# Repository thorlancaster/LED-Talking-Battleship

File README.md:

# LED-Talking-Battleship
Talking Battleship implemented on a 12x12 LED grid with an ATMega328 processor

This project is composed of:
* A Control PCB that contains the main circuitry and power supplies
* A LED display PCB that drives an 12x12 grid of RGB LEDs. You'll need to make 4 of these.
* Code to run the above boards
* A compiled audio file you'll need to write to the SPI Flash chip for audio functionality
 (If you leave the flash chip blank, the game will not play audio)

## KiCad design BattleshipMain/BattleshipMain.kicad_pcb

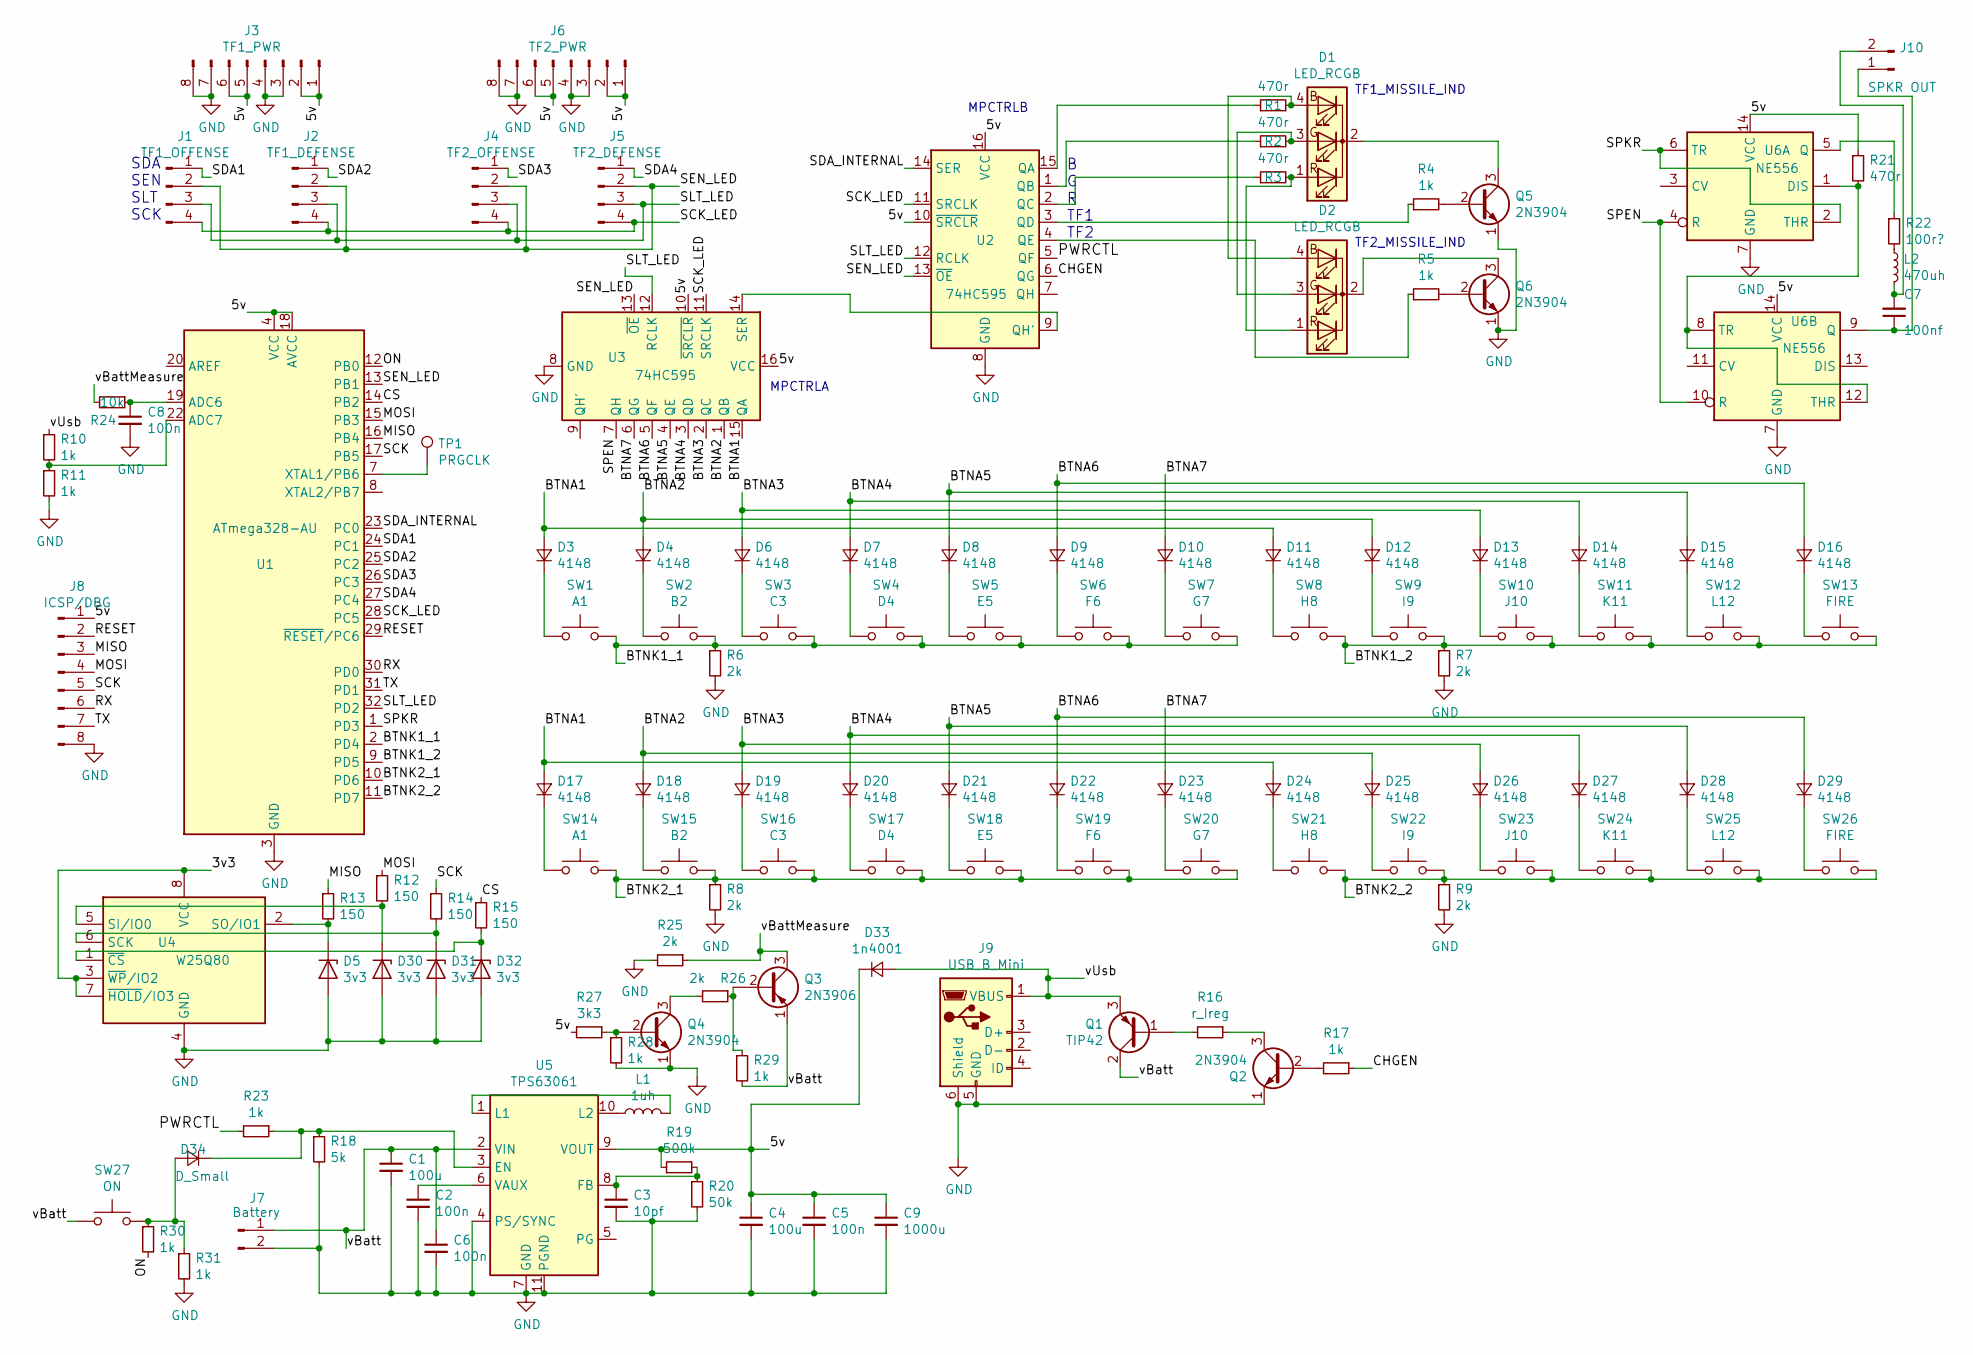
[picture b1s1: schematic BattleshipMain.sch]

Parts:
C1, C4: 100u; CP_Radial_D10.0mm_P2.50mm
C2, C5, C6, C8: 100n; C_0805_2012Metric
C3: 10pf; C_0805_2012Metric
C7: 100nf; C_0805_2012Metric
C9: 1000u; CP_Radial_D10.0mm_P7.50mm
D1, D2: LED_RCGB; LED_D5.0mm-4_RGB
D3, D4, D6, D7, D8, D9, D10, D11, D12, D13, D14, D15, D16, D17, D18, D19, D20, D21, D22, D23, D24, D25, D26, D27, D28, D29: 4148; D_DO-34_SOD68_P7.62mm_Horizontal
D5, D30, D31, D32: 3v3; D_DO-34_SOD68_P7.62mm_Horizontal
D33: 1n4001; D_DO-15_P10.16mm_Horizontal
D34: D_Small; D_DO-15_P10.16mm_Horizontal
J1: TF1_OFFENSE; PinHeader_1x04_P2.54mm_Vertical
J2: TF1_DEFENSE; PinHeader_1x04_P2.54mm_Vertical
J3: TF1_PWR; PinHeader_1x08_P2.54mm_Vertical
J4: TF2_OFFENSE; PinHeader_1x04_P2.54mm_Vertical
J5: TF2_DEFENSE; PinHeader_1x04_P2.54mm_Vertical
J6: TF2_PWR; PinHeader_1x08_P2.54mm_Vertical
J7: Battery; PinHeader_1x02_P2.54mm_Vertical
J8: ICSP/DBG; PinHeader_1x08_P2.54mm_Vertical
J9: USB_B_Mini; USB_Mini-B_Lumberg_2486_01_Horizontal
J10: SPKR OUT; PinHeader_1x02_P2.54mm_Vertical
L1: 1uh; L_Bourns-SRR1005
L2: 470uh; R_Axial_DIN0204_L3.6mm_D1.6mm_P7.62mm_Horizontal
Q1: TIP42; TO-220-3_Vertical
Q2, Q4, Q5, Q6: 2N3904; TO-92_Inline
Q3: 2N3906; TO-92_Inline
R1, R2, R3, R21: 470r; R_Axial_DIN0204_L3.6mm_D1.6mm_P7.62mm_Horizontal
R4, R5, R10, R11, R17, R23, R28, R29, R30, R31: 1k; R_Axial_DIN0207_L6.3mm_D2.5mm_P7.62mm_Horizontal
R6, R7, R8, R9, R25, R26: 2k; R_Axial_DIN0207_L6.3mm_D2.5mm_P7.62mm_Horizontal
R12, R13, R14, R15: 150; R_Axial_DIN0204_L3.6mm_D1.6mm_P7.62mm_Horizontal
R16: r_Ireg; R_Axial_DIN0207_L6.3mm_D2.5mm_P7.62mm_Horizontal
R18: 5k; R_Axial_DIN0207_L6.3mm_D2.5mm_P7.62mm_Horizontal
R19: 500k; R_Axial_DIN0207_L6.3mm_D2.5mm_P7.62mm_Horizontal
R20: 50k; R_Axial_DIN0207_L6.3mm_D2.5mm_P7.62mm_Horizontal
R22: 100r?; R_Axial_DIN0207_L6.3mm_D2.5mm_P7.62mm_Horizontal
R24: 10k; R_Axial_DIN0207_L6.3mm_D2.5mm_P7.62mm_Horizontal
R27: 3k3; R_Axial_DIN0207_L6.3mm_D2.5mm_P7.62mm_Horizontal
SW1, SW14: A1; Push_E-Switch_KS01Q01_RubberPad
SW2, SW15: B2; Push_E-Switch_KS01Q01_RubberPad
SW3, SW16: C3; Push_E-Switch_KS01Q01_RubberPad
SW4, SW17: D4; Push_E-Switch_KS01Q01_RubberPad
SW5, SW18: E5; Push_E-Switch_KS01Q01_RubberPad
SW6, SW19: F6; Push_E-Switch_KS01Q01_RubberPad
SW7, SW20: G7; Push_E-Switch_KS01Q01_RubberPad
SW8, SW21: H8; Push_E-Switch_KS01Q01_RubberPad
SW9, SW22: I9; Push_E-Switch_KS01Q01_RubberPad
SW10, SW23: J10; Push_E-Switch_KS01Q01_RubberPad
SW11, SW24: K11; Push_E-Switch_KS01Q01_RubberPad
SW12, SW25: L12; Push_E-Switch_KS01Q01_RubberPad
SW13, SW26: FIRE; Push_E-Switch_KS01Q01_RubberPad
SW27: ON; Push_E-Switch_KS01Q01_RubberPad
TP1: PRGCLK; TestPoint_Pad_2.5x2.5mm
U1: ATmega328-AU; TQFP-32_7x7mm_P0.8mm
U2, U3: 74HC595; DIP-16_W7.62mm
U4: W25Q80; SOIC-8_3.9x4.9mm_P1.27mm
U5: TPS63061; Texas_S-PWSON-N10_ThermalVias
U6: NE556; DIP-16_W7.62mm

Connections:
/3v3: U4.3 (~WP~/IO2), U4.7 (~HOLD~/IO3), U4.8 (VCC)
/5v: C4.1, C5.1, C9.1, D33.1 (K), J3.1, J3.2, J3.5, J3.6, J6.1, J6.2, J6.5, J6.6, J8.1, R19.1, R21.1, R27.2, U1.4 (VCC), U1.6 (VCC), U1.18 (AVCC), U2.10 (~SRCLR), U2.16 (VCC), U3.10 (~SRCLR), U3.16 (VCC), U5.9 (VOUT), U6.14 (VCC)
/BTNA1: D3.2 (A), D11.2 (A), D17.2 (A), D24.2 (A), U3.15 (QA)
/BTNA2: D4.2 (A), D12.2 (A), D18.2 (A), D25.2 (A), U3.1 (QB)
/BTNA3: D6.2 (A), D13.2 (A), D19.2 (A), D26.2 (A), U3.2 (QC)
/BTNA4: D7.2 (A), D14.2 (A), D20.2 (A), D27.2 (A), U3.3 (QD)
/BTNA5: D8.2 (A), D15.2 (A), D21.2 (A), D28.2 (A), U3.4 (QE)
/BTNA6: D9.2 (A), D16.2 (A), D22.2 (A), D29.2 (A), U3.5 (QF)
/BTNA7: D10.2 (A), D23.2 (A), U3.6 (QG)
/BTNK1_1: R6.1, SW1.2, SW2.2, SW3.2, SW4.2, SW5.2, SW6.2, SW7.2, U1.2 (PD4)
/BTNK1_2: R7.1, SW8.2, SW9.2, SW10.2, SW11.2, SW12.2, SW13.2, U1.9 (PD5)
/BTNK2_1: R8.1, SW14.2, SW15.2, SW16.2, SW17.2, SW18.2, SW19.2, SW20.2, U1.10 (PD6)
/BTNK2_2: R9.1, SW21.2, SW22.2, SW23.2, SW24.2, SW25.2, SW26.2, U1.11 (PD7)
/CS: R15.1, U1.14 (PB2)
/MISO: J8.3, R13.1, U1.16 (PB4)
/MOSI: J8.4, R12.1, U1.15 (PB3)
/ON: R30.2, U1.12 (PB0)
/RESET: J8.2, U1.29 (~RESET~/PC6)
/RX: J8.6, U1.30 (PD0)
/SCK: J8.5, R14.1, U1.17 (PB5)
/SDA1: J1.1, U1.24 (PC1)
/SDA2: J2.1, U1.25 (PC2)
/SDA3: J4.1, U1.26 (PC3)
/SDA4: J5.1, U1.27 (PC4)
/SDA_INTERNAL: U1.23 (PC0), U2.14 (SER)
/SEN_LED: J1.2, J2.2, J4.2, J5.2, U1.13 (PB1), U2.13 (~OE), U3.13 (~OE)
/SPEN: U3.7 (QH), U6.4 (R), U6.10 (R)
/SPKR: U1.1 (PD3), U6.2 (THR), U6.6 (TR)
/TX: J8.7, U1.31 (PD1)
/vBatt: C1.1, C6.1, J7.1, Q1.2 (C), Q3.1 (E), R29.2, SW27.1, U5.2 (VIN)
/vBattMeasure: Q3.3 (C), R24.2, R25.1
/vUsb: D33.2 (A), J9.1 (VBUS), Q1.3 (E), R10.1
GND: C1.2, C2.2, C3.2, C4.2, C5.2, C6.2, C8.2, C9.2, D5.2 (A), D30.2 (A), D31.2 (A), D32.2 (A), J3.3, J3.4, J3.7, J3.8, J6.3, J6.4, J6.7, J6.8, J7.2, J8.8, J9.5 (GND), J9.6 (Shield), Q2.1 (E), Q4.1 (E), Q5.1 (E), Q6.1 (E), R6.2, R7.2, R8.2, R9.2, R11.2, R18.2, R20.2, R25.2, R28.2, R31.2, U1.3 (GND), U1.5 (GND), U1.21 (GND), U2.8 (GND), U3.8 (GND), U4.4 (GND), U5.4 (PS/SYNC), U5.7 (GND), U5.11 (PGND), U6.7 (GND)
unnamed: C2.1, U5.6 (VAUX)
unnamed: C3.1, R19.2, R20.1, U5.8 (FB)
unnamed: C7.1, J10.1, U6.9 (Q)
unnamed: C7.2, J10.2, L2.2
unnamed: C8.1, R24.1, U1.19 (ADC6)
unnamed: D1.1 (RA), D2.1 (RA), R3.2
unnamed: D1.2 (K), Q5.3 (C)
unnamed: D1.3 (GA), D2.3 (GA), R2.2
unnamed: D1.4 (BA), D2.4 (BA), R1.2
unnamed: D2.2 (K), Q6.3 (C)
unnamed: D3.1 (K), SW1.1
unnamed: D4.1 (K), SW2.1
unnamed: D5.1 (K), R13.2, U4.2 (SO/IO1)
unnamed: D6.1 (K), SW3.1
unnamed: D7.1 (K), SW4.1
unnamed: D8.1 (K), SW5.1
unnamed: D9.1 (K), SW6.1
unnamed: D10.1 (K), SW7.1
unnamed: D11.1 (K), SW8.1
unnamed: D12.1 (K), SW9.1
unnamed: D13.1 (K), SW10.1
unnamed: D14.1 (K), SW11.1
unnamed: D15.1 (K), SW12.1
unnamed: D16.1 (K), SW13.1
unnamed: D17.1 (K), SW14.1
unnamed: D18.1 (K), SW15.1
unnamed: D19.1 (K), SW16.1
unnamed: D20.1 (K), SW17.1
unnamed: D21.1 (K), SW18.1
unnamed: D22.1 (K), SW19.1
unnamed: D23.1 (K), SW20.1
unnamed: D24.1 (K), SW21.1
unnamed: D25.1 (K), SW22.1
unnamed: D26.1 (K), SW23.1
unnamed: D27.1 (K), SW24.1
unnamed: D28.1 (K), SW25.1
unnamed: D29.1 (K), SW26.1
unnamed: D30.1 (K), R12.2, U4.5 (SI/IO0)
unnamed: D31.1 (K), R14.2, U4.6 (SCK)
unnamed: D32.1 (K), R15.2, U4.1 (~CS)
unnamed: D34.1 (K), R18.1, R23.1, U5.3 (EN)
unnamed: D34.2 (A), R30.1, R31.1, SW27.2
unnamed: L1.1, U5.10 (L2)
unnamed: L1.2, U5.1 (L1)
unnamed: L2.1, R22.2
unnamed: Q1.1 (B), R16.2
unnamed: Q2.2 (B), R17.2
unnamed: Q2.3 (C), R16.1
unnamed: Q3.2 (B), R26.1, R29.1
unnamed: Q4.2 (B), R27.1, R28.1
unnamed: Q4.3 (C), R26.2
unnamed: Q5.2 (B), R4.2
unnamed: Q6.2 (B), R5.2
unnamed: R1.1, U2.15 (QA)
unnamed: R2.1, U2.1 (QB)
unnamed: R3.1, U2.2 (QC)
unnamed: R4.1, U2.3 (QD)
unnamed: R5.1, U2.4 (QE)
unnamed: R10.2, R11.1, U1.22 (ADC7)
unnamed: R21.2, U6.1 (DIS), U6.8 (TR), U6.12 (THR)
unnamed: R22.1, U6.5 (Q)
unnamed: U2.9 (QH'), U3.14 (SER)

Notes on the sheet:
SDA SEN SLT SCK
TF1_MISSILE_IND
TF2_MISSILE_IND
B G R TF1 TF2
MPCTRLB
MPCTRLA

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
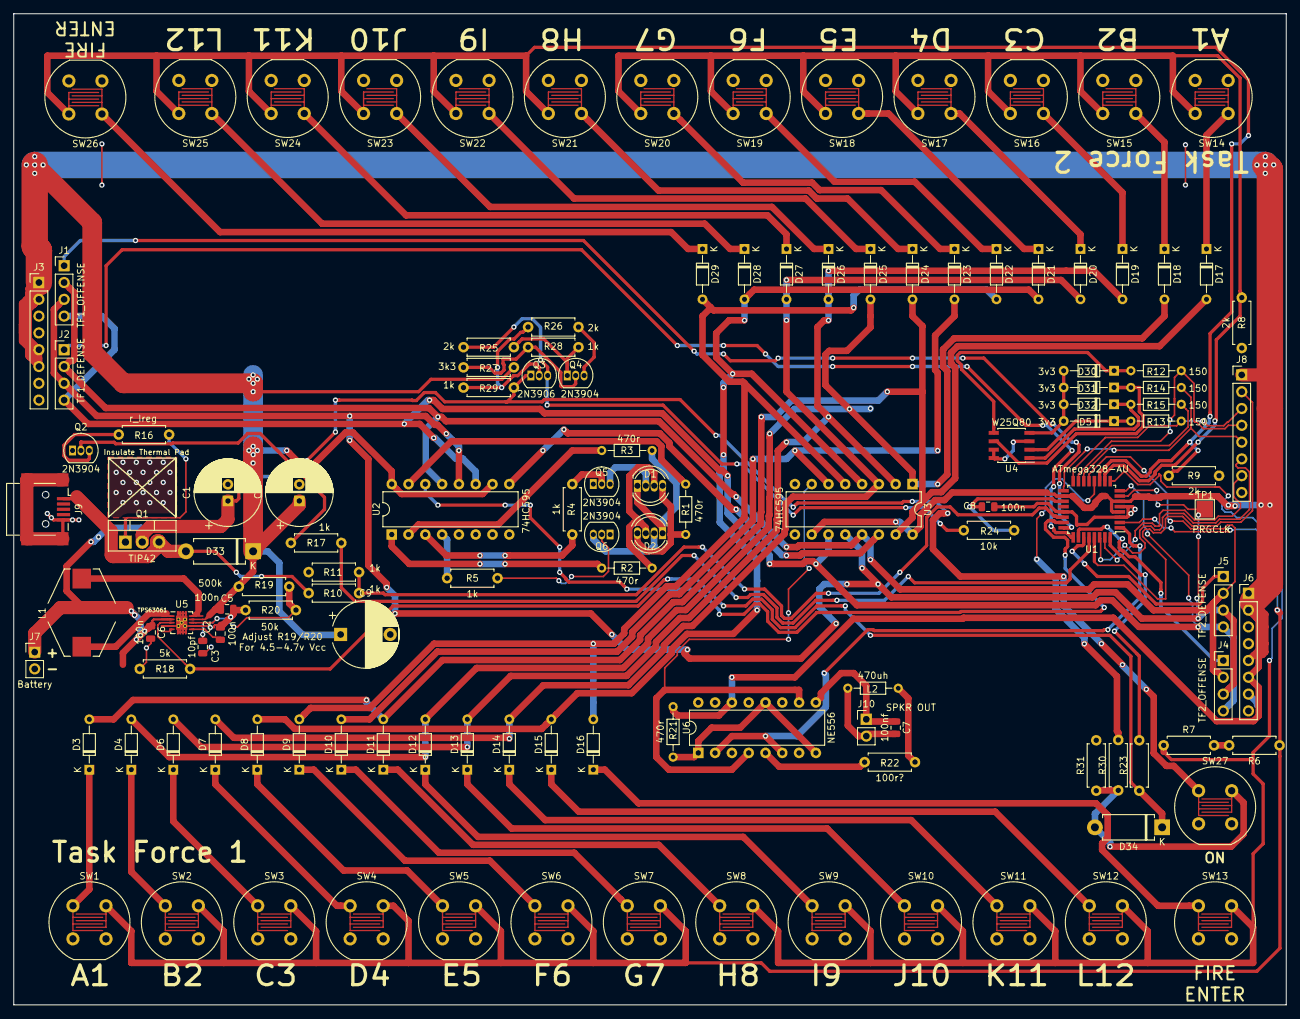
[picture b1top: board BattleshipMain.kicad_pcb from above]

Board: 2 copper layers, 192.4 x 149.9 mm, 126 parts (0 on the bottom side), 99 nets.

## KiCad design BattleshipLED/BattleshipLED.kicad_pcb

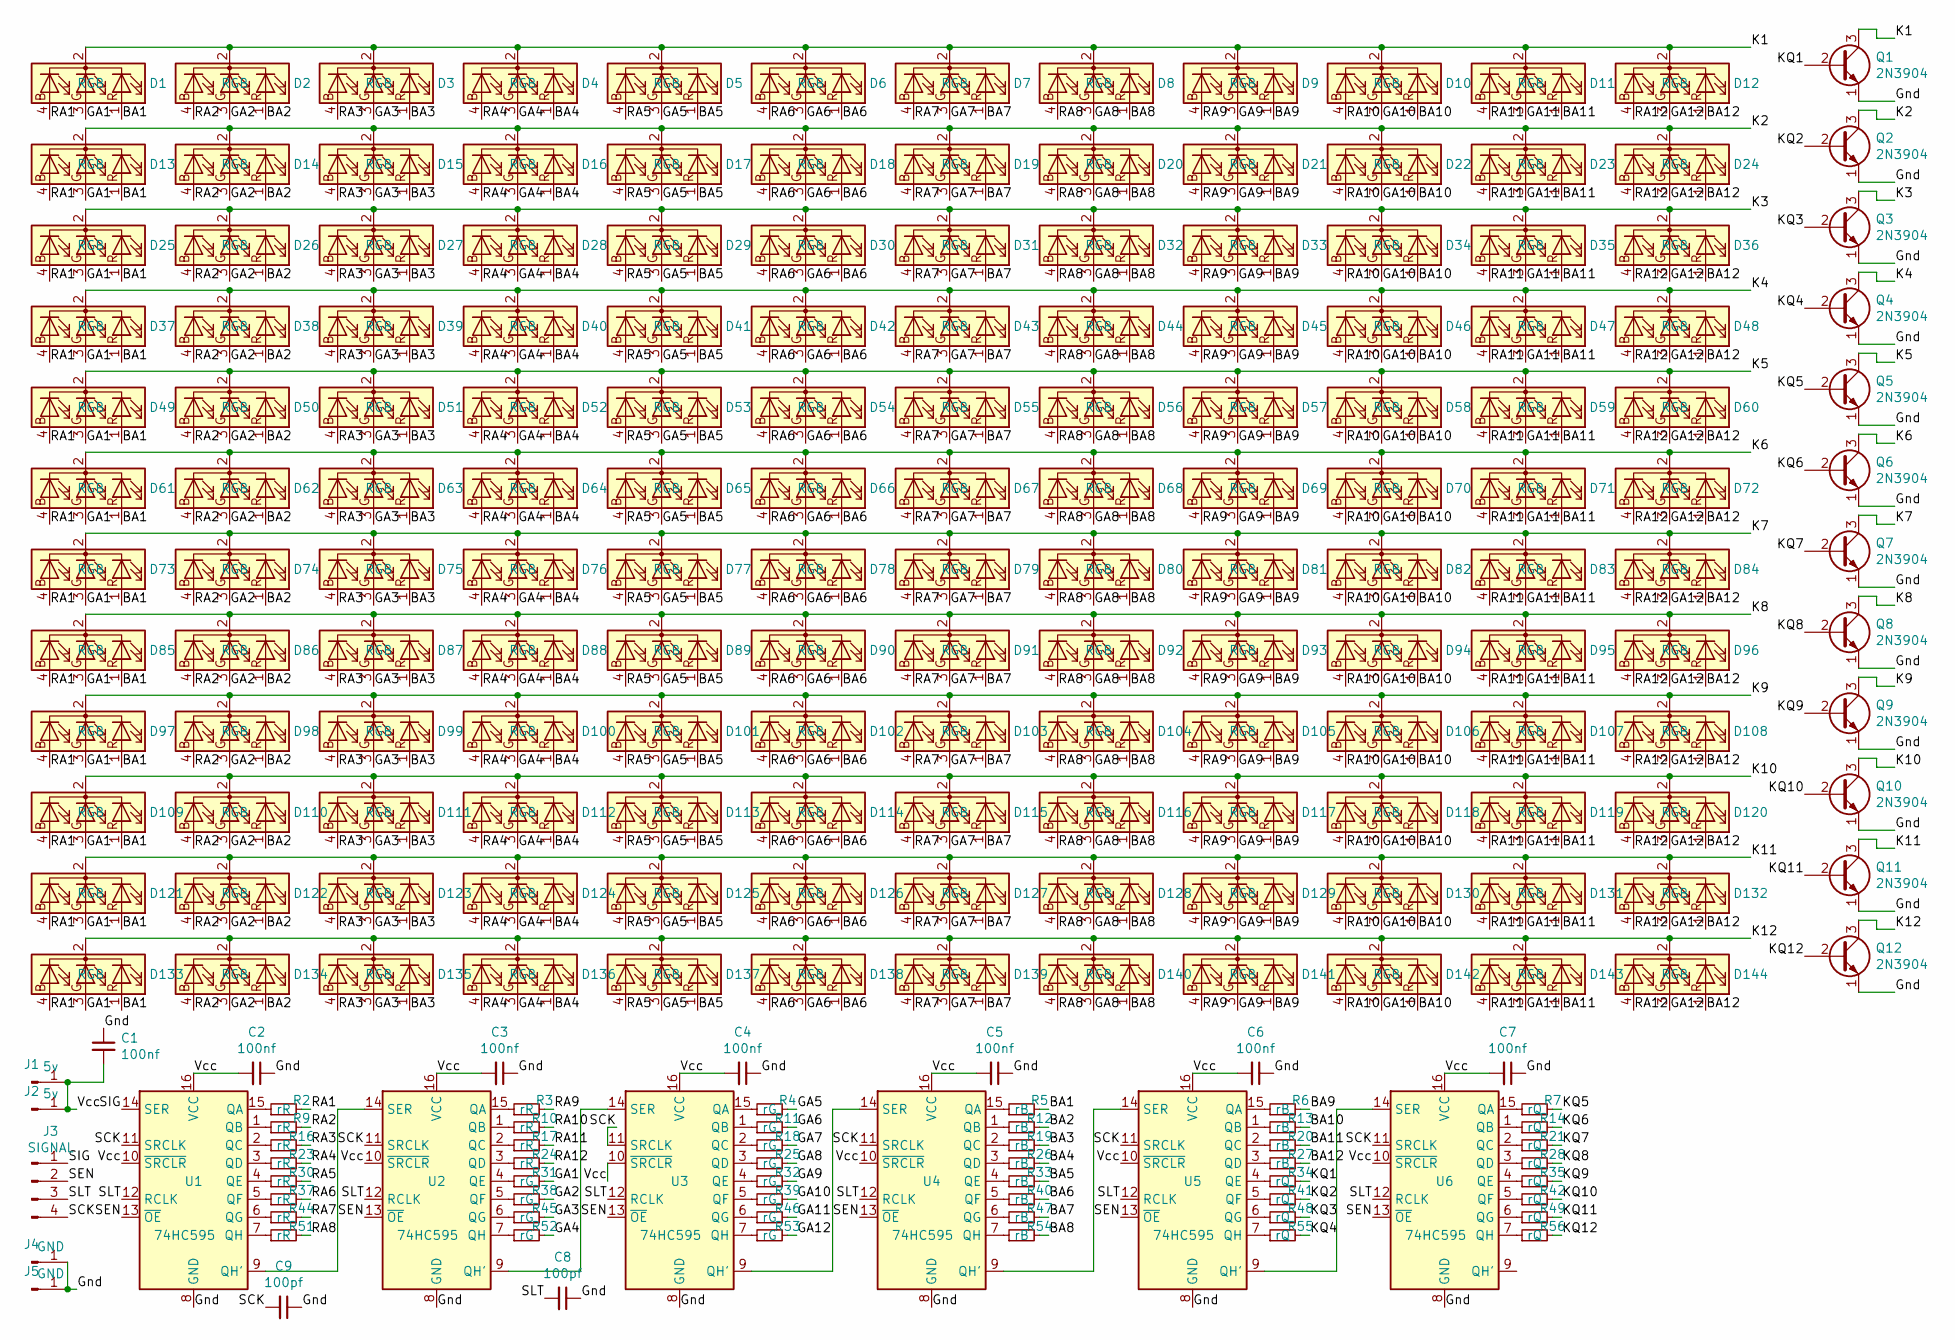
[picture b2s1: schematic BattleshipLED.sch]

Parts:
C1, C2, C3, C4, C5, C6, C7: 100nf; C_0805_2012Metric
C8, C9: 100pf; C_0805_2012Metric
D1, D2, D3, D4, D5, D6, D7, D8, D9, D10, D11, D12, D13, D14, D15, D16, D17, D18, D19, D20, D21, D22, D23, D24, D25, D26, D27, D28, D29, D30, D31, D32, D33, D34, D35, D36, D37, D38, D39, D40, D41, D42, D43, D44, D45, D46, D47, D48, D49, D50, D51, D52, D53, D54, D55, D56, D57, D58, D59, D60, D61, D62, D63, D64, D65, D66, D67, D68, D69, D70, D71, D72, D73, D74, D75, D76, D77, D78, D79, D80, D81, D82, D83, D84, D85, D86, D87, D88, D89, D90, D91, D92, D93, D94, D95, D96, D97, D98, D99, D100, D101, D102, D103, D104, D105, D106, D107, D108, D109, D110, D111, D112, D113, D114, D115, D116, D117, D118, D119, D120, D121, D122, D123, D124, D125, D126, D127, D128, D129, D130, D131, D132, D133, D134, D135, D136, D137, D138, D139, D140, D141, D142, D143, D144: RGB; LED_D5.0mm-4_RGB
J1, J2: 5v; PinHeader_1x01_P2.54mm_Vertical
J3: SIGNAL; PinHeader_1x04_P2.54mm_Vertical
J4, J5: GND; PinHeader_1x01_P2.54mm_Vertical
Q1, Q2, Q3, Q4, Q5, Q6, Q7, Q8, Q9, Q10, Q11, Q12: 2N3904; TO-92_Inline
R2, R3, R9, R10, R16, R17, R23, R24, R30, R37, R44, R51: rR; R_Axial_DIN0204_L3.6mm_D1.6mm_P7.62mm_Horizontal
R4, R11, R18, R25, R31, R32, R38, R39, R45, R46, R52, R53: rG; R_Axial_DIN0204_L3.6mm_D1.6mm_P7.62mm_Horizontal
R5, R6, R12, R13, R19, R20, R26, R27, R33, R40, R47, R54: rB; R_Axial_DIN0204_L3.6mm_D1.6mm_P7.62mm_Horizontal
R7, R14, R21, R28, R34, R35, R41, R42, R48, R49, R55, R56: rQ; R_Axial_DIN0204_L3.6mm_D1.6mm_P7.62mm_Horizontal
U1, U2, U3, U4, U5, U6: 74HC595; DIP-16_W7.62mm

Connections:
/BA1: D1.1 (RA), D13.1 (RA), D25.1 (RA), D37.1 (RA), D49.1 (RA), D61.1 (RA), D73.1 (RA), D85.1 (RA), D97.1 (RA), D109.1 (RA), D121.1 (RA), D133.1 (RA), R5.2
/BA2: D2.1 (RA), D14.1 (RA), D26.1 (RA), D38.1 (RA), D50.1 (RA), D62.1 (RA), D74.1 (RA), D86.1 (RA), D98.1 (RA), D110.1 (RA), D122.1 (RA), D134.1 (RA), R12.2
/BA3: D3.1 (RA), D15.1 (RA), D27.1 (RA), D39.1 (RA), D51.1 (RA), D63.1 (RA), D75.1 (RA), D87.1 (RA), D99.1 (RA), D111.1 (RA), D123.1 (RA), D135.1 (RA), R19.2
/BA4: D4.1 (RA), D16.1 (RA), D28.1 (RA), D40.1 (RA), D52.1 (RA), D64.1 (RA), D76.1 (RA), D88.1 (RA), D100.1 (RA), D112.1 (RA), D124.1 (RA), D136.1 (RA), R26.2
/BA5: D5.1 (RA), D17.1 (RA), D29.1 (RA), D41.1 (RA), D53.1 (RA), D65.1 (RA), D77.1 (RA), D89.1 (RA), D101.1 (RA), D113.1 (RA), D125.1 (RA), D137.1 (RA), R33.2
/BA6: D6.1 (RA), D18.1 (RA), D30.1 (RA), D42.1 (RA), D54.1 (RA), D66.1 (RA), D78.1 (RA), D90.1 (RA), D102.1 (RA), D114.1 (RA), D126.1 (RA), D138.1 (RA), R40.2
/BA7: D7.1 (RA), D19.1 (RA), D31.1 (RA), D43.1 (RA), D55.1 (RA), D67.1 (RA), D79.1 (RA), D91.1 (RA), D103.1 (RA), D115.1 (RA), D127.1 (RA), D139.1 (RA), R47.2
/BA8: D8.1 (RA), D20.1 (RA), D32.1 (RA), D44.1 (RA), D56.1 (RA), D68.1 (RA), D80.1 (RA), D92.1 (RA), D104.1 (RA), D116.1 (RA), D128.1 (RA), D140.1 (RA), R54.2
/BA9: D9.1 (RA), D21.1 (RA), D33.1 (RA), D45.1 (RA), D57.1 (RA), D69.1 (RA), D81.1 (RA), D93.1 (RA), D105.1 (RA), D117.1 (RA), D129.1 (RA), D141.1 (RA), R6.2
/BA10: D10.1 (RA), D22.1 (RA), D34.1 (RA), D46.1 (RA), D58.1 (RA), D70.1 (RA), D82.1 (RA), D94.1 (RA), D106.1 (RA), D118.1 (RA), D130.1 (RA), D142.1 (RA), R13.2
/BA11: D11.1 (RA), D23.1 (RA), D35.1 (RA), D47.1 (RA), D59.1 (RA), D71.1 (RA), D83.1 (RA), D95.1 (RA), D107.1 (RA), D119.1 (RA), D131.1 (RA), D143.1 (RA), R20.2
/BA12: D12.1 (RA), D24.1 (RA), D36.1 (RA), D48.1 (RA), D60.1 (RA), D72.1 (RA), D84.1 (RA), D96.1 (RA), D108.1 (RA), D120.1 (RA), D132.1 (RA), D144.1 (RA), R27.2
/GA1: D1.3 (GA), D13.3 (GA), D25.3 (GA), D37.3 (GA), D49.3 (GA), D61.3 (GA), D73.3 (GA), D85.3 (GA), D97.3 (GA), D109.3 (GA), D121.3 (GA), D133.3 (GA), R31.2
/GA2: D2.3 (GA), D14.3 (GA), D26.3 (GA), D38.3 (GA), D50.3 (GA), D62.3 (GA), D74.3 (GA), D86.3 (GA), D98.3 (GA), D110.3 (GA), D122.3 (GA), D134.3 (GA), R38.2
/GA3: D3.3 (GA), D15.3 (GA), D27.3 (GA), D39.3 (GA), D51.3 (GA), D63.3 (GA), D75.3 (GA), D87.3 (GA), D99.3 (GA), D111.3 (GA), D123.3 (GA), D135.3 (GA), R45.2
/GA4: D4.3 (GA), D16.3 (GA), D28.3 (GA), D40.3 (GA), D52.3 (GA), D64.3 (GA), D76.3 (GA), D88.3 (GA), D100.3 (GA), D112.3 (GA), D124.3 (GA), D136.3 (GA), R52.2
/GA5: D5.3 (GA), D17.3 (GA), D29.3 (GA), D41.3 (GA), D53.3 (GA), D65.3 (GA), D77.3 (GA), D89.3 (GA), D101.3 (GA), D113.3 (GA), D125.3 (GA), D137.3 (GA), R4.2
/GA6: D6.3 (GA), D18.3 (GA), D30.3 (GA), D42.3 (GA), D54.3 (GA), D66.3 (GA), D78.3 (GA), D90.3 (GA), D102.3 (GA), D114.3 (GA), D126.3 (GA), D138.3 (GA), R11.2
/GA7: D7.3 (GA), D19.3 (GA), D31.3 (GA), D43.3 (GA), D55.3 (GA), D67.3 (GA), D79.3 (GA), D91.3 (GA), D103.3 (GA), D115.3 (GA), D127.3 (GA), D139.3 (GA), R18.2
/GA8: D8.3 (GA), D20.3 (GA), D32.3 (GA), D44.3 (GA), D56.3 (GA), D68.3 (GA), D80.3 (GA), D92.3 (GA), D104.3 (GA), D116.3 (GA), D128.3 (GA), D140.3 (GA), R25.2
/GA9: D9.3 (GA), D21.3 (GA), D33.3 (GA), D45.3 (GA), D57.3 (GA), D69.3 (GA), D81.3 (GA), D93.3 (GA), D105.3 (GA), D117.3 (GA), D129.3 (GA), D141.3 (GA), R32.2
/GA10: D10.3 (GA), D22.3 (GA), D34.3 (GA), D46.3 (GA), D58.3 (GA), D70.3 (GA), D82.3 (GA), D94.3 (GA), D106.3 (GA), D118.3 (GA), D130.3 (GA), D142.3 (GA), R39.2
/GA11: D11.3 (GA), D23.3 (GA), D35.3 (GA), D47.3 (GA), D59.3 (GA), D71.3 (GA), D83.3 (GA), D95.3 (GA), D107.3 (GA), D119.3 (GA), D131.3 (GA), D143.3 (GA), R46.2
/GA12: D12.3 (GA), D24.3 (GA), D36.3 (GA), D48.3 (GA), D60.3 (GA), D72.3 (GA), D84.3 (GA), D96.3 (GA), D108.3 (GA), D120.3 (GA), D132.3 (GA), D144.3 (GA), R53.2
/Gnd: C1.1, C2.1, C3.1, C4.1, C5.1, C6.1, C7.1, C8.1, C9.1, J4.1, J5.1, Q1.1 (E), Q2.1 (E), Q3.1 (E), Q4.1 (E), Q5.1 (E), Q6.1 (E), Q7.1 (E), Q8.1 (E), Q9.1 (E), Q10.1 (E), Q11.1 (E), Q12.1 (E), U1.8 (GND), U2.8 (GND), U3.8 (GND), U4.8 (GND), U5.8 (GND), U6.8 (GND)
/K1: D1.2 (K), D2.2 (K), D3.2 (K), D4.2 (K), D5.2 (K), D6.2 (K), D7.2 (K), D8.2 (K), D9.2 (K), D10.2 (K), D11.2 (K), D12.2 (K), Q1.3 (C)
/K2: D13.2 (K), D14.2 (K), D15.2 (K), D16.2 (K), D17.2 (K), D18.2 (K), D19.2 (K), D20.2 (K), D21.2 (K), D22.2 (K), D23.2 (K), D24.2 (K), Q2.3 (C)
/K3: D25.2 (K), D26.2 (K), D27.2 (K), D28.2 (K), D29.2 (K), D30.2 (K), D31.2 (K), D32.2 (K), D33.2 (K), D34.2 (K), D35.2 (K), D36.2 (K), Q3.3 (C)
/K4: D37.2 (K), D38.2 (K), D39.2 (K), D40.2 (K), D41.2 (K), D42.2 (K), D43.2 (K), D44.2 (K), D45.2 (K), D46.2 (K), D47.2 (K), D48.2 (K), Q4.3 (C)
/K5: D49.2 (K), D50.2 (K), D51.2 (K), D52.2 (K), D53.2 (K), D54.2 (K), D55.2 (K), D56.2 (K), D57.2 (K), D58.2 (K), D59.2 (K), D60.2 (K), Q5.3 (C)
/K6: D61.2 (K), D62.2 (K), D63.2 (K), D64.2 (K), D65.2 (K), D66.2 (K), D67.2 (K), D68.2 (K), D69.2 (K), D70.2 (K), D71.2 (K), D72.2 (K), Q6.3 (C)
/K7: D73.2 (K), D74.2 (K), D75.2 (K), D76.2 (K), D77.2 (K), D78.2 (K), D79.2 (K), D80.2 (K), D81.2 (K), D82.2 (K), D83.2 (K), D84.2 (K), Q7.3 (C)
/K8: D85.2 (K), D86.2 (K), D87.2 (K), D88.2 (K), D89.2 (K), D90.2 (K), D91.2 (K), D92.2 (K), D93.2 (K), D94.2 (K), D95.2 (K), D96.2 (K), Q8.3 (C)
/K9: D97.2 (K), D98.2 (K), D99.2 (K), D100.2 (K), D101.2 (K), D102.2 (K), D103.2 (K), D104.2 (K), D105.2 (K), D106.2 (K), D107.2 (K), D108.2 (K), Q9.3 (C)
/K10: D109.2 (K), D110.2 (K), D111.2 (K), D112.2 (K), D113.2 (K), D114.2 (K), D115.2 (K), D116.2 (K), D117.2 (K), D118.2 (K), D119.2 (K), D120.2 (K), Q10.3 (C)
/K11: D121.2 (K), D122.2 (K), D123.2 (K), D124.2 (K), D125.2 (K), D126.2 (K), D127.2 (K), D128.2 (K), D129.2 (K), D130.2 (K), D131.2 (K), D132.2 (K), Q11.3 (C)
/K12: D133.2 (K), D134.2 (K), D135.2 (K), D136.2 (K), D137.2 (K), D138.2 (K), D139.2 (K), D140.2 (K), D141.2 (K), D142.2 (K), D143.2 (K), D144.2 (K), Q12.3 (C)
/KQ1: Q1.2 (B), R34.2
/KQ2: Q2.2 (B), R41.2
/KQ3: Q3.2 (B), R48.2
/KQ4: Q4.2 (B), R55.2
/KQ5: Q5.2 (B), R7.2
/KQ6: Q6.2 (B), R14.2
/KQ7: Q7.2 (B), R21.2
/KQ8: Q8.2 (B), R28.2
/KQ9: Q9.2 (B), R35.2
/KQ10: Q10.2 (B), R42.2
/KQ11: Q11.2 (B), R49.2
/KQ12: Q12.2 (B), R56.2
/RA1: D1.4 (BA), D13.4 (BA), D25.4 (BA), D37.4 (BA), D49.4 (BA), D61.4 (BA), D73.4 (BA), D85.4 (BA), D97.4 (BA), D109.4 (BA), D121.4 (BA), D133.4 (BA), R2.2
/RA2: D2.4 (BA), D14.4 (BA), D26.4 (BA), D38.4 (BA), D50.4 (BA), D62.4 (BA), D74.4 (BA), D86.4 (BA), D98.4 (BA), D110.4 (BA), D122.4 (BA), D134.4 (BA), R9.2
/RA3: D3.4 (BA), D15.4 (BA), D27.4 (BA), D39.4 (BA), D51.4 (BA), D63.4 (BA), D75.4 (BA), D87.4 (BA), D99.4 (BA), D111.4 (BA), D123.4 (BA), D135.4 (BA), R16.2
/RA4: D4.4 (BA), D16.4 (BA), D28.4 (BA), D40.4 (BA), D52.4 (BA), D64.4 (BA), D76.4 (BA), D88.4 (BA), D100.4 (BA), D112.4 (BA), D124.4 (BA), D136.4 (BA), R23.2
/RA5: D5.4 (BA), D17.4 (BA), D29.4 (BA), D41.4 (BA), D53.4 (BA), D65.4 (BA), D77.4 (BA), D89.4 (BA), D101.4 (BA), D113.4 (BA), D125.4 (BA), D137.4 (BA), R30.2
/RA6: D6.4 (BA), D18.4 (BA), D30.4 (BA), D42.4 (BA), D54.4 (BA), D66.4 (BA), D78.4 (BA), D90.4 (BA), D102.4 (BA), D114.4 (BA), D126.4 (BA), D138.4 (BA), R37.2
/RA7: D7.4 (BA), D19.4 (BA), D31.4 (BA), D43.4 (BA), D55.4 (BA), D67.4 (BA), D79.4 (BA), D91.4 (BA), D103.4 (BA), D115.4 (BA), D127.4 (BA), D139.4 (BA), R44.2
/RA8: D8.4 (BA), D20.4 (BA), D32.4 (BA), D44.4 (BA), D56.4 (BA), D68.4 (BA), D80.4 (BA), D92.4 (BA), D104.4 (BA), D116.4 (BA), D128.4 (BA), D140.4 (BA), R51.2
/RA9: D9.4 (BA), D21.4 (BA), D33.4 (BA), D45.4 (BA), D57.4 (BA), D69.4 (BA), D81.4 (BA), D93.4 (BA), D105.4 (BA), D117.4 (BA), D129.4 (BA), D141.4 (BA), R3.2
/RA10: D10.4 (BA), D22.4 (BA), D34.4 (BA), D46.4 (BA), D58.4 (BA), D70.4 (BA), D82.4 (BA), D94.4 (BA), D106.4 (BA), D118.4 (BA), D130.4 (BA), D142.4 (BA), R10.2
/RA11: D11.4 (BA), D23.4 (BA), D35.4 (BA), D47.4 (BA), D59.4 (BA), D71.4 (BA), D83.4 (BA), D95.4 (BA), D107.4 (BA), D119.4 (BA), D131.4 (BA), D143.4 (BA), R17.2
/RA12: D12.4 (BA), D24.4 (BA), D36.4 (BA), D48.4 (BA), D60.4 (BA), D72.4 (BA), D84.4 (BA), D96.4 (BA), D108.4 (BA), D120.4 (BA), D132.4 (BA), D144.4 (BA), R24.2
/SCK: C9.2, J3.4, U1.11 (SRCLK), U2.11 (SRCLK), U3.11 (SRCLK), U4.11 (SRCLK), U5.11 (SRCLK), U6.11 (SRCLK)
/SEN: J3.2, U1.13 (~OE), U2.13 (~OE), U3.13 (~OE), U4.13 (~OE), U5.13 (~OE), U6.13 (~OE)
/SIG: J3.1, U1.14 (SER)
/SLT: C8.2, J3.3, U1.12 (RCLK), U2.12 (RCLK), U3.12 (RCLK), U4.12 (RCLK), U5.12 (RCLK), U6.12 (RCLK)
/Vcc: C1.2, C2.2, C3.2, C4.2, C5.2, C6.2, C7.2, J1.1, J2.1, U1.10 (~SRCLR), U1.16 (VCC), U2.10 (~SRCLR), U2.16 (VCC), U3.10 (~SRCLR), U3.16 (VCC), U4.10 (~SRCLR), U4.16 (VCC), U5.10 (~SRCLR), U5.16 (VCC), U6.10 (~SRCLR), U6.16 (VCC)
unnamed: R2.1, U1.15 (QA)
unnamed: R3.1, U2.15 (QA)
unnamed: R4.1, U3.15 (QA)
unnamed: R5.1, U4.15 (QA)
unnamed: R6.1, U5.15 (QA)
unnamed: R7.1, U6.15 (QA)
unnamed: R9.1, U1.1 (QB)
unnamed: R10.1, U2.1 (QB)
unnamed: R11.1, U3.1 (QB)
unnamed: R12.1, U4.1 (QB)
unnamed: R13.1, U5.1 (QB)
unnamed: R14.1, U6.1 (QB)
unnamed: R16.1, U1.2 (QC)
unnamed: R17.1, U2.2 (QC)
unnamed: R18.1, U3.2 (QC)
unnamed: R19.1, U4.2 (QC)
unnamed: R20.1, U5.2 (QC)
unnamed: R21.1, U6.2 (QC)
unnamed: R23.1, U1.3 (QD)
unnamed: R24.1, U2.3 (QD)
unnamed: R25.1, U3.3 (QD)
unnamed: R26.1, U4.3 (QD)
unnamed: R27.1, U5.3 (QD)
unnamed: R28.1, U6.3 (QD)
unnamed: R30.1, U1.4 (QE)
unnamed: R31.1, U2.4 (QE)
unnamed: R32.1, U3.4 (QE)
unnamed: R33.1, U4.4 (QE)
unnamed: R34.1, U5.4 (QE)
unnamed: R35.1, U6.4 (QE)
unnamed: R37.1, U1.5 (QF)
unnamed: R38.1, U2.5 (QF)
unnamed: R39.1, U3.5 (QF)
unnamed: R40.1, U4.5 (QF)
unnamed: R41.1, U5.5 (QF)
unnamed: R42.1, U6.5 (QF)
unnamed: R44.1, U1.6 (QG)
unnamed: R45.1, U2.6 (QG)
unnamed: R46.1, U3.6 (QG)
unnamed: R47.1, U4.6 (QG)
unnamed: R48.1, U5.6 (QG)
unnamed: R49.1, U6.6 (QG)
unnamed: R51.1, U1.7 (QH)
unnamed: R52.1, U2.7 (QH)
unnamed: R53.1, U3.7 (QH)
unnamed: R54.1, U4.7 (QH)
unnamed: R55.1, U5.7 (QH)
unnamed: R56.1, U6.7 (QH)
unnamed: U1.9 (QH'), U2.14 (SER)
unnamed: U2.9 (QH'), U3.14 (SER)
unnamed: U3.9 (QH'), U4.14 (SER)
unnamed: U4.9 (QH'), U5.14 (SER)
unnamed: U5.9 (QH'), U6.14 (SER)

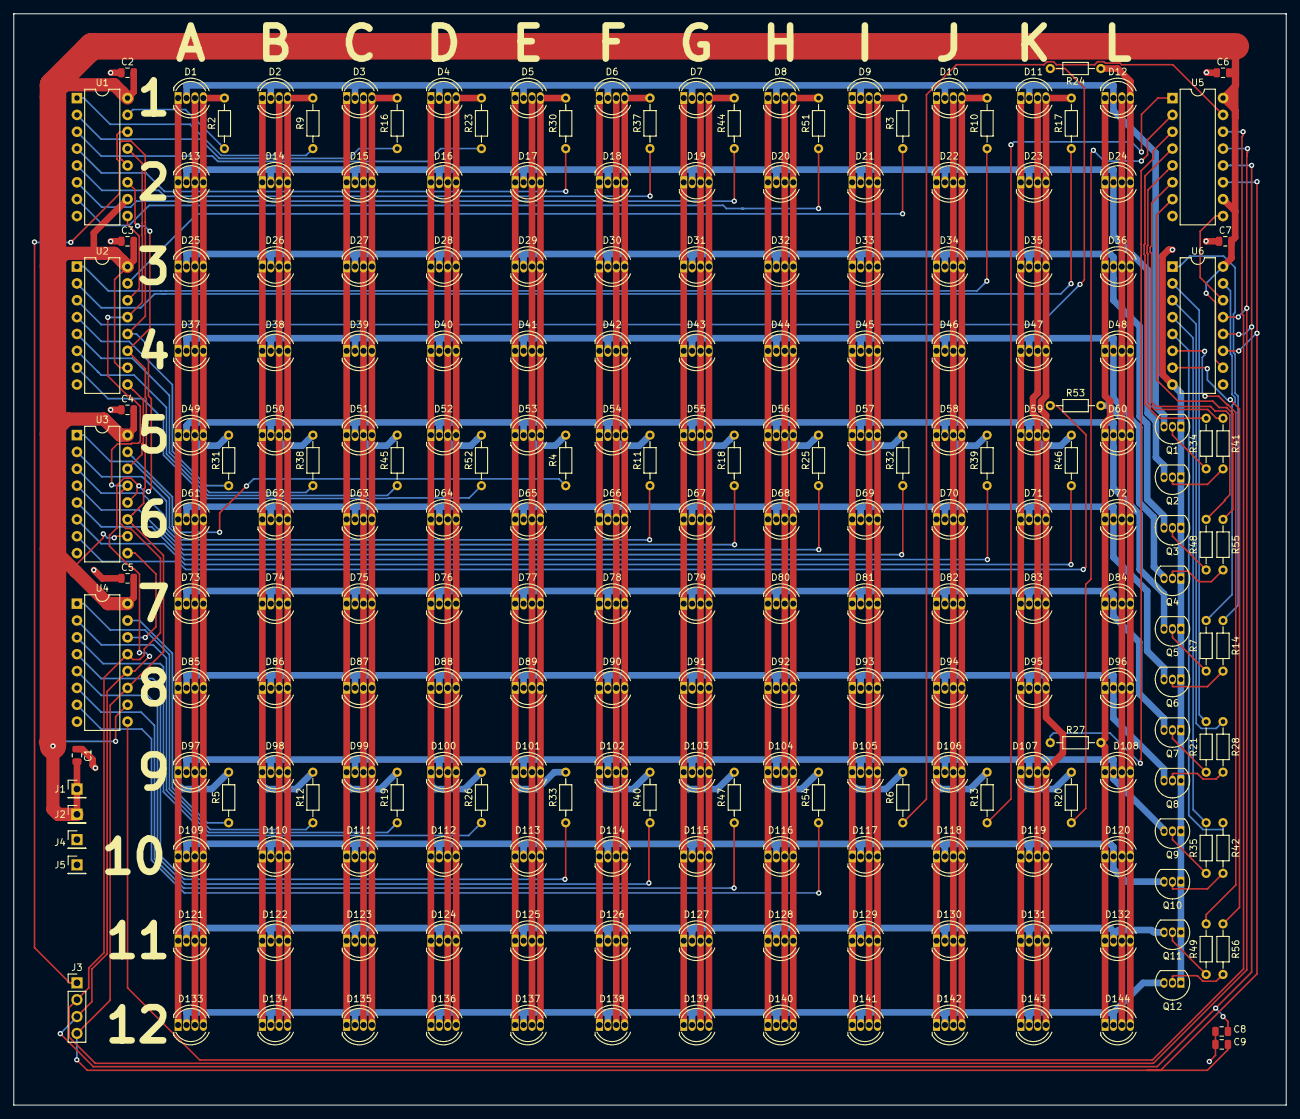
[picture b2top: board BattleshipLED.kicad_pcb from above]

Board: 2 copper layers, 191.8 x 164.5 mm, 224 parts (0 on the bottom side), 119 nets.

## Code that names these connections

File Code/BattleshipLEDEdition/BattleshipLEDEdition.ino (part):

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
#define DBG_FLASH_REDRAW 0

const int SPKR = 3;
#define BATT_CAL_VALUE 1.56923 // How many ticks of internal voltmeter per millivolt of battery
#define VUSB_CAL_VALUE 0.81769 // ... of USB voltage
#define BATT_LVC_WARN 3580 // Battery millivolts where game warns of low battery
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
// Serial data bus for LEDs
#define SDA_PORT PORTC
const int SDA_INTERNAL = A0;
const int SDA_TF1_OFFENSE = A1;
const int SDA_TF1_DEFENSE = A2;
const int SDA_TF2_OFFENSE = A3;
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#define BOARD_TF1_DEFENSE 1
#define BOARD_TF2_OFFENSE 2
#define BOARD_TF2_DEFENSE 3
const int CHGEN = A5;
#define SEN_LED_PORT PORTB
#define SEN_LED_DDR DDRB
#define SLT_LED_PORT PORTD
#define SLT_LED_DDR DDRD
#define SCK_LED_PORT PORTC
#define SCK_LED_DDR PORTC
#define SEN_LED_PIN 1
#define SLT_LED_PIN 2
#define SCK_LED_PIN 5
#define BTNK_PORT PIND
#define BTNK_11 4
#define BTNK_12 5
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  // Prevent bug where reboot occurred instead of shutdown due to capacitors not fully discharging
  _delay_ms(100);
  // Set pins
  pinMode(SPKR, OUTPUT);
  pinMode(SDA_INTERNAL, OUTPUT);
  pinMode(SDA_TF1_OFFENSE, OUTPUT);
  pinMode(SDA_TF1_DEFENSE, OUTPUT);
  pinMode(SDA_TF2_OFFENSE, OUTPUT);
  pinMode(SDA_TF2_DEFENSE, OUTPUT);
  pinMode(CHGEN, OUTPUT);
  // Set pins that aren't Arduino pins
  SEN_LED_DDR |= (1 << SEN_LED_PIN);
  SLT_LED_DDR |= (1 << SLT_LED_PIN);
  SCK_LED_DDR |= (1 << SCK_LED_PIN);

  // Set up speaker
  analogWrite(SPKR, 127);
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
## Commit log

2022-12-23 Add Code
2022-12-23 Add audio
